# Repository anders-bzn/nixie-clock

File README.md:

# About the Nixie Clock

This is a clock powered by a Raspberry Pi Zero W. It fetches current time by 
NTP and must be connected to a WiFi network to display the time.

The time is displayed on six IN-14 nixie tubes driven by six 74141. No 
multiplexing! The intensity can be adjusted by PWM.

## PCB's 
There are in total five PCB's in this project. All boards are drawn with KiCad 8.0.

### Board nixie-bottom
Bottom lid, no electrical function.

### Board nixie-clock
The main board, it hold gpio-expanders and driver IC's for the tubes. It
also connects to the PSU board, Raspberry Pi and the nixie tube board.

### Board nixie-clock-psu
Power supply board, creates 5V DC and 170V DC from 12V DC. The 170V is created by a step up converter built using a MAX1771 IC. The 5V is created by a integrated switched regulator.

### Board nixie-clock-tubes
Upper board on which all tubes are mounted.

### Board nixie-top
Top lid, no electrical function.

### Software
The clocks software is written in Python. It's just a simple poll loop that set the new time on gpio's on the gpio-expanders every time the second changes. It's started as a systemd service at boot time.

To install the software on the Raspberry Pi, copy the [./sw](sw/) folder to the Raspberry Pi and install the software by:

```
$ sudo ./clock-setup.sh
$ sudo reboot
```

NOTE: [./sw/timesyncd.conf](sw/timesyncd.conf) is an example.

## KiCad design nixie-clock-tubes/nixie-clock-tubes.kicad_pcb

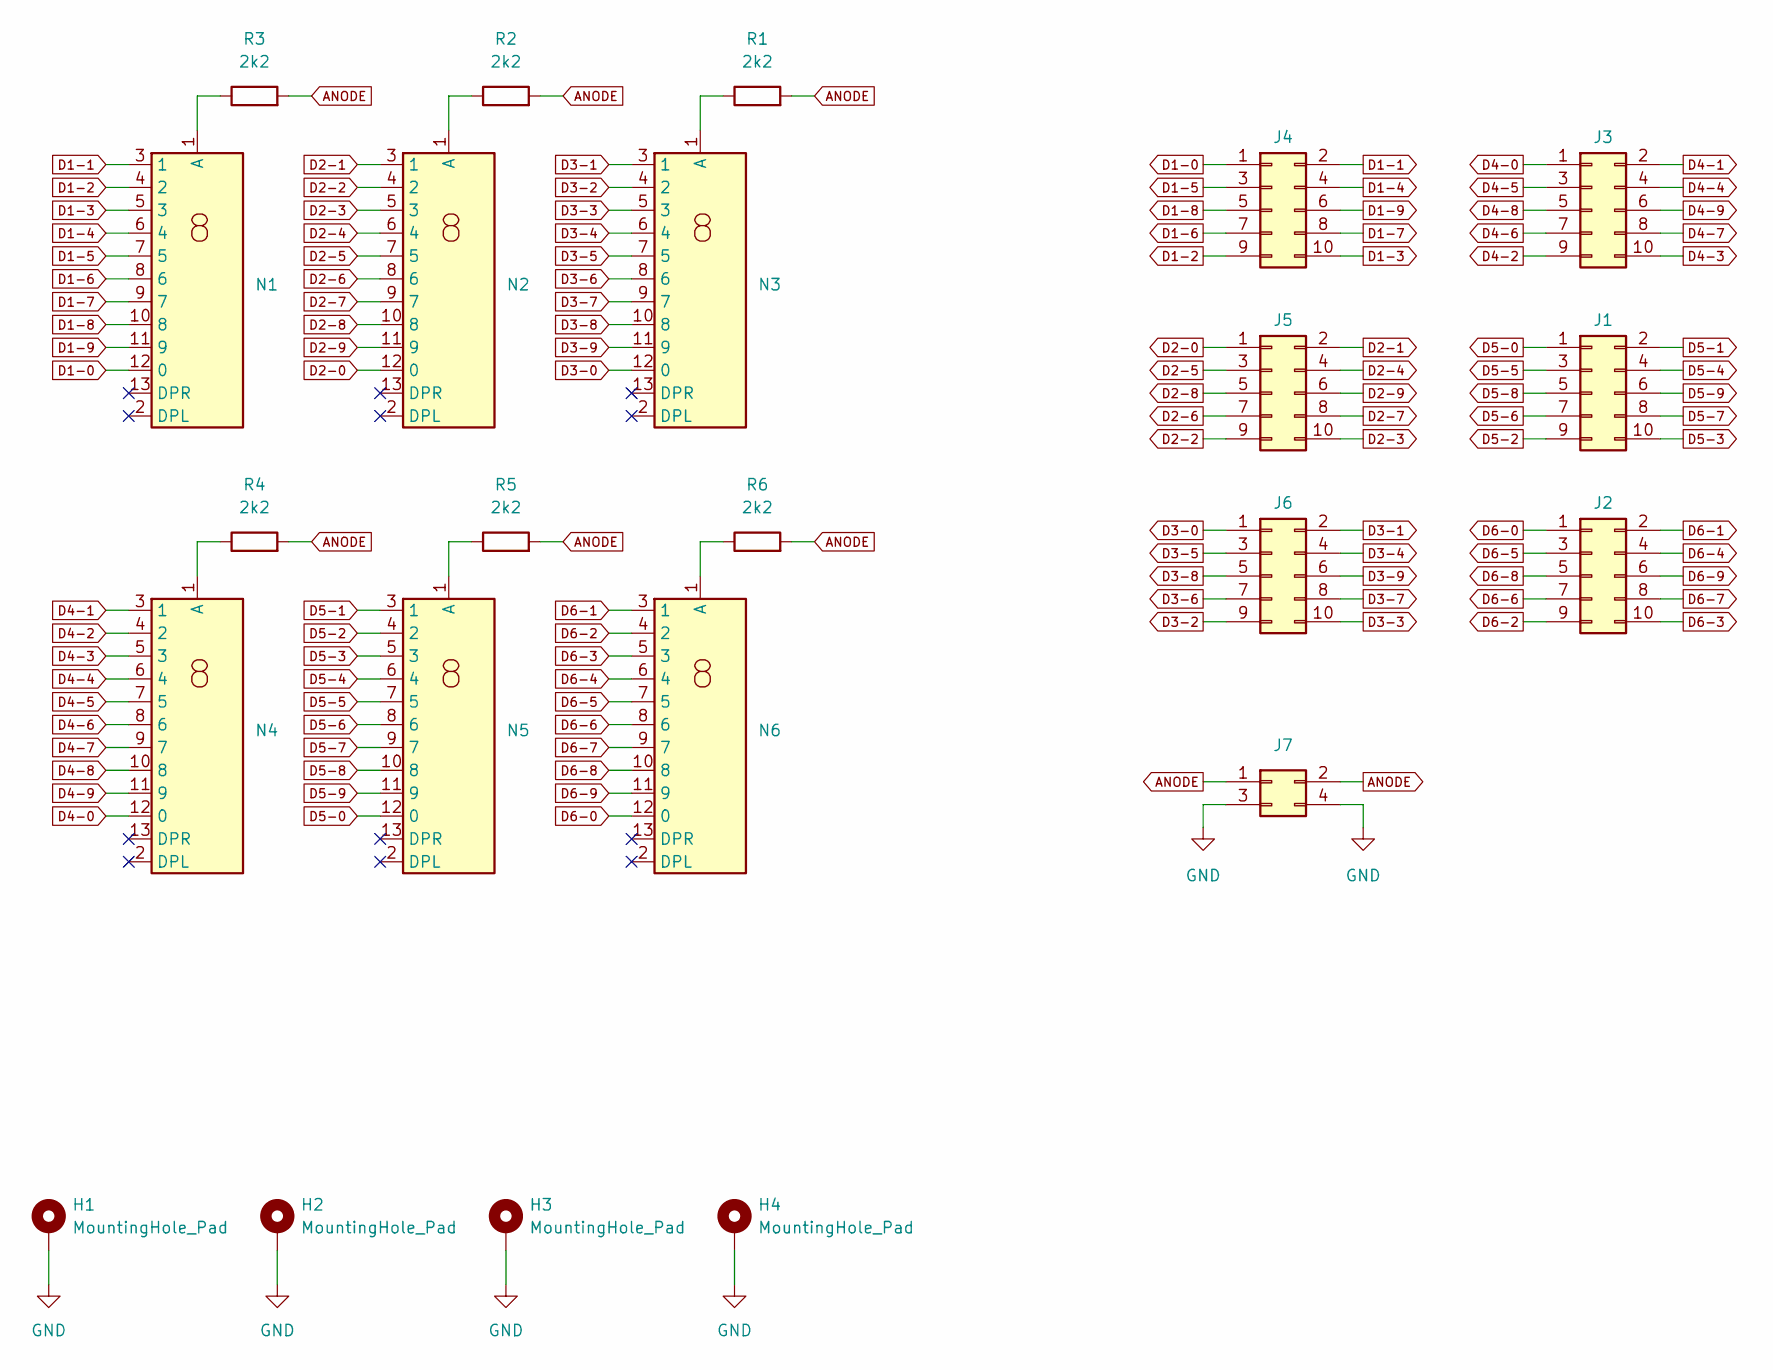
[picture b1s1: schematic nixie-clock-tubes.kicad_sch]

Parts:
H1, H2, H3, H4: MountingHole_Pad; MountingHole_2.7mm_M2.5_DIN965_Pad
J1, J2, J3, J4, J5, J6: Conn_02x05_Odd_Even; PinSocket_2x05_P2.00mm_Vertical
J7: Conn_02x02_Odd_Even; PinSocket_2x02_P2.00mm_Vertical
N1, N2, N3, N4, N5, N6: IN-14
R1, R2, R3, R4, R5, R6: 2k2; R_1206_3216Metric

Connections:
ANODE: J7.1, J7.2, R1.2, R2.2, R3.2, R4.2, R5.2, R6.2
D1-0: J4.1, N1.12 (0)
D1-1: J4.2, N1.3 (1)
D1-2: J4.9, N1.4 (2)
D1-3: J4.10, N1.5 (3)
D1-4: J4.4, N1.6 (4)
D1-5: J4.3, N1.7 (5)
D1-6: J4.7, N1.8 (6)
D1-7: J4.8, N1.9 (7)
D1-8: J4.5, N1.10 (8)
D1-9: J4.6, N1.11 (9)
D2-0: J5.1, N2.12 (0)
D2-1: J5.2, N2.3 (1)
D2-2: J5.9, N2.4 (2)
D2-3: J5.10, N2.5 (3)
D2-4: J5.4, N2.6 (4)
D2-5: J5.3, N2.7 (5)
D2-6: J5.7, N2.8 (6)
D2-7: J5.8, N2.9 (7)
D2-8: J5.5, N2.10 (8)
D2-9: J5.6, N2.11 (9)
D3-0: J6.1, N3.12 (0)
D3-1: J6.2, N3.3 (1)
D3-2: J6.9, N3.4 (2)
D3-3: J6.10, N3.5 (3)
D3-4: J6.4, N3.6 (4)
D3-5: J6.3, N3.7 (5)
D3-6: J6.7, N3.8 (6)
D3-7: J6.8, N3.9 (7)
D3-8: J6.5, N3.10 (8)
D3-9: J6.6, N3.11 (9)
D4-0: J3.1, N4.12 (0)
D4-1: J3.2, N4.3 (1)
D4-2: J3.9, N4.4 (2)
D4-3: J3.10, N4.5 (3)
D4-4: J3.4, N4.6 (4)
D4-5: J3.3, N4.7 (5)
D4-6: J3.7, N4.8 (6)
D4-7: J3.8, N4.9 (7)
D4-8: J3.5, N4.10 (8)
D4-9: J3.6, N4.11 (9)
D5-0: J1.1, N5.12 (0)
D5-1: J1.2, N5.3 (1)
D5-2: J1.9, N5.4 (2)
D5-3: J1.10, N5.5 (3)
D5-4: J1.4, N5.6 (4)
D5-5: J1.3, N5.7 (5)
D5-6: J1.7, N5.8 (6)
D5-7: J1.8, N5.9 (7)
D5-8: J1.5, N5.10 (8)
D5-9: J1.6, N5.11 (9)
D6-0: J2.1, N6.12 (0)
D6-1: J2.2, N6.3 (1)
D6-2: J2.9, N6.4 (2)
D6-3: J2.10, N6.5 (3)
D6-4: J2.4, N6.6 (4)
D6-5: J2.3, N6.7 (5)
D6-6: J2.7, N6.8 (6)
D6-7: J2.8, N6.9 (7)
D6-8: J2.5, N6.10 (8)
D6-9: J2.6, N6.11 (9)
GND: H1.1, H2.1, H3.1, H4.1, J7.3, J7.4
unnamed: N1.1 (A), R3.1
unnamed: N2.1 (A), R2.1
unnamed: N3.1 (A), R1.1
unnamed: N4.1 (A), R4.1
unnamed: N5.1 (A), R5.1
unnamed: N6.1 (A), R6.1

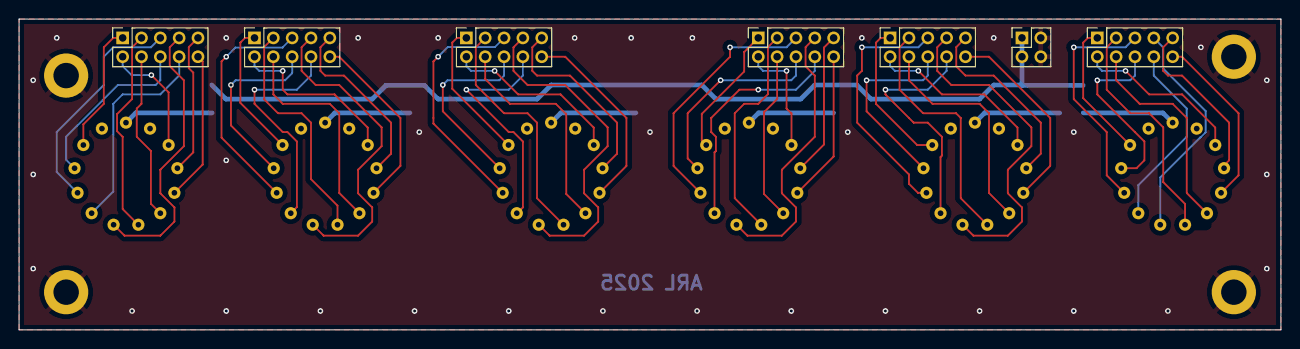
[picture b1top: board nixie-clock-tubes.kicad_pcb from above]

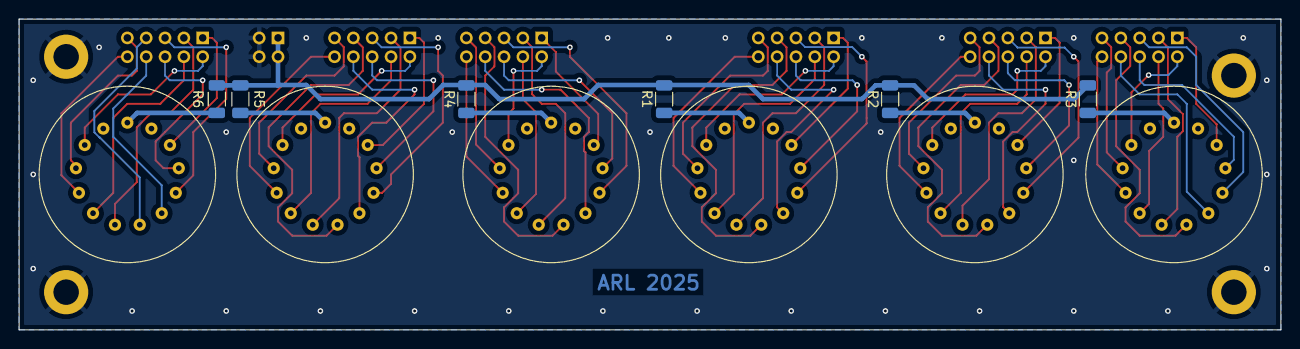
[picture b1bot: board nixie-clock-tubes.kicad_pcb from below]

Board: 2 copper layers, 134.0 x 33.0 mm, 23 parts (12 on the bottom side), 68 nets.

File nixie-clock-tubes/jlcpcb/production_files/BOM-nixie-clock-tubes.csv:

Comment,Designator,Footprint,LCSC,Quantity
~,N6,IN-14,,1
~,N5,IN-14,,1
~,N4,IN-14,,1
~,N3,IN-14,,1
~,N2,IN-14,,1
~,N1,IN-14,,1
Conn_02x02_Odd_Even,J7,PinSocket_2x02_P2.00mm_Vertical,,1
Conn_02x05_Odd_Even,J6,PinSocket_2x05_P2.00mm_Vertical,,1
Conn_02x05_Odd_Even,J5,PinSocket_2x05_P2.00mm_Vertical,,1
Conn_02x05_Odd_Even,J4,PinSocket_2x05_P2.00mm_Vertical,,1
Conn_02x05_Odd_Even,J3,PinSocket_2x05_P2.00mm_Vertical,,1
Conn_02x05_Odd_Even,J2,PinSocket_2x05_P2.00mm_Vertical,,1
Conn_02x05_Odd_Even,J1,PinSocket_2x05_P2.00mm_Vertical,,1
2k2,R6,R_1206_3216Metric,,1
2k2,R5,R_1206_3216Metric,,1
2k2,R4,R_1206_3216Metric,,1
2k2,R3,R_1206_3216Metric,,1
2k2,R2,R_1206_3216Metric,,1
2k2,R1,R_1206_3216Metric,,1

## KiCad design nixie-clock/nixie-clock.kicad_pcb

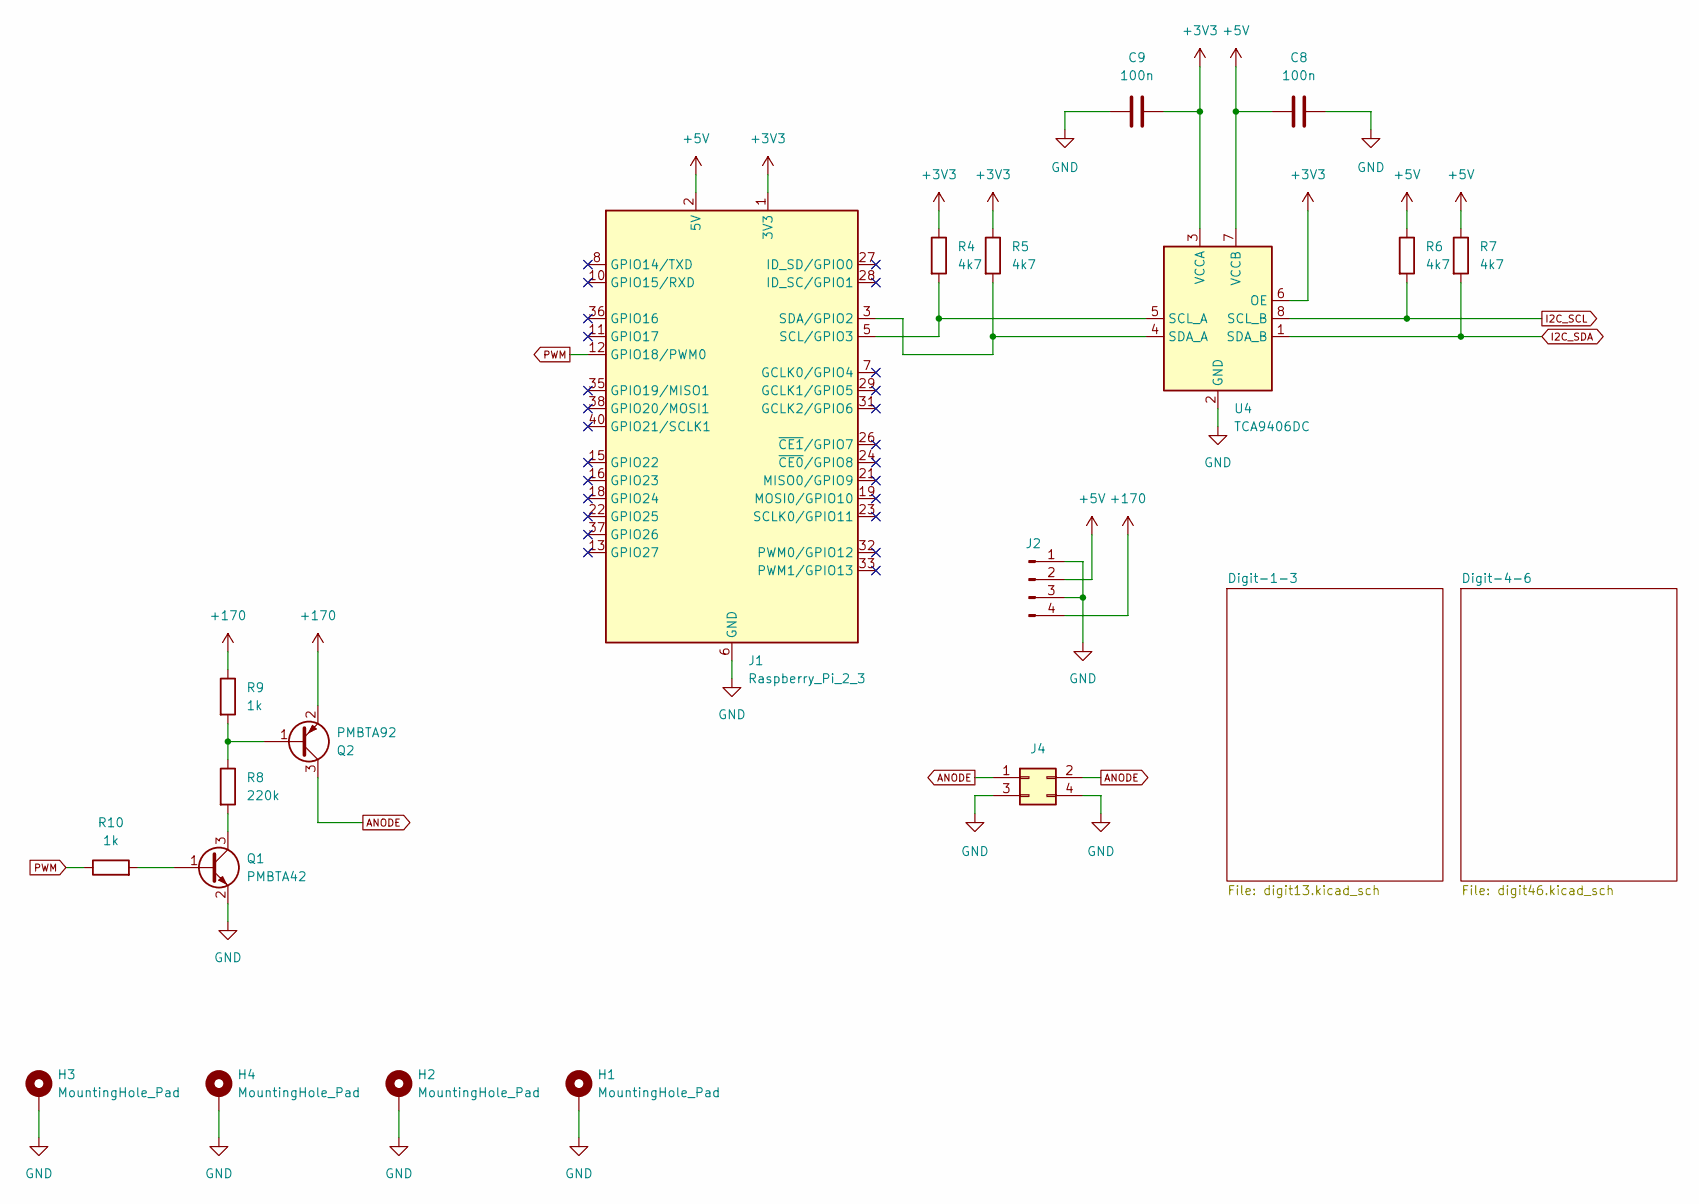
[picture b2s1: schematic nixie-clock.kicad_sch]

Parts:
C8, C9: 100n; C_0805_2012Metric_Pad1.18x1.45mm_HandSolder
H1, H2, H3, H4: MountingHole_Pad; MountingHole_2.7mm_M2.5_DIN965_Pad
J1: Raspberry_Pi_2_3; Raspberry_Pi_Zero_Socketed_THT_FaceDown_MountingHoles
J2: Conn_01x04_Pin; PinHeader_1x04_P2.54mm_Vertical
J4: Conn_02x02_Odd_Even; PinHeader_2x02_P2.00mm_Vertical
Q1: PMBTA42; SOT-23
Q2: PMBTA92; SOT-23
R4, R5, R6, R7: 4k7; R_0805_2012Metric_Pad1.20x1.40mm_HandSolder
R8: 220k; R_1206_3216Metric_Pad1.30x1.75mm_HandSolder
R9: 1k; R_1206_3216Metric_Pad1.30x1.75mm_HandSolder
R10: 1k; R_0805_2012Metric_Pad1.20x1.40mm_HandSolder
U4: TCA9406DC; SSOP-8_2.95x2.8mm_P0.65mm

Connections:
+3V3: C9.1, J1.1 (3V3), J1.17 (3V3), R4.1, R5.1, U4.3 (VCCA), U4.6 (OE)
+5V: C8.1, J1.2 (5V), J1.4 (5V), J2.2, R6.1, R7.1, U4.7 (VCCB); also elsewhere on the board
+170: J2.4, Q2.2 (E), R9.1
ANODE: J4.1, J4.2, Q2.3 (C)
GND: C8.2, C9.2, H1.1, H2.1, H3.1, H4.1, J1.6 (GND), J1.9 (GND), J1.14 (GND), J1.20 (GND), J1.25 (GND), J1.30 (GND), J1.34 (GND), J1.39 (GND), J2.1, J2.3, J4.3, J4.4, Q1.2 (E), U4.2 (GND); also elsewhere on the board
I2C_SCL: R6.2, U4.8 (SCL_B); also elsewhere on the board
I2C_SDA: R7.2, U4.1 (SDA_B); also elsewhere on the board
unnamed: J1.5 (SCL/GPIO3), R4.2, U4.5 (SCL_A)
unnamed: J1.3 (SDA/GPIO2), R5.2, U4.4 (SDA_A)
unnamed: Q1.1 (B), R10.2
unnamed: Q1.3 (C), R8.2
unnamed: Q2.1 (B), R8.1, R9.2
PWM: J1.12 (GPIO18/PWM0), R10.1

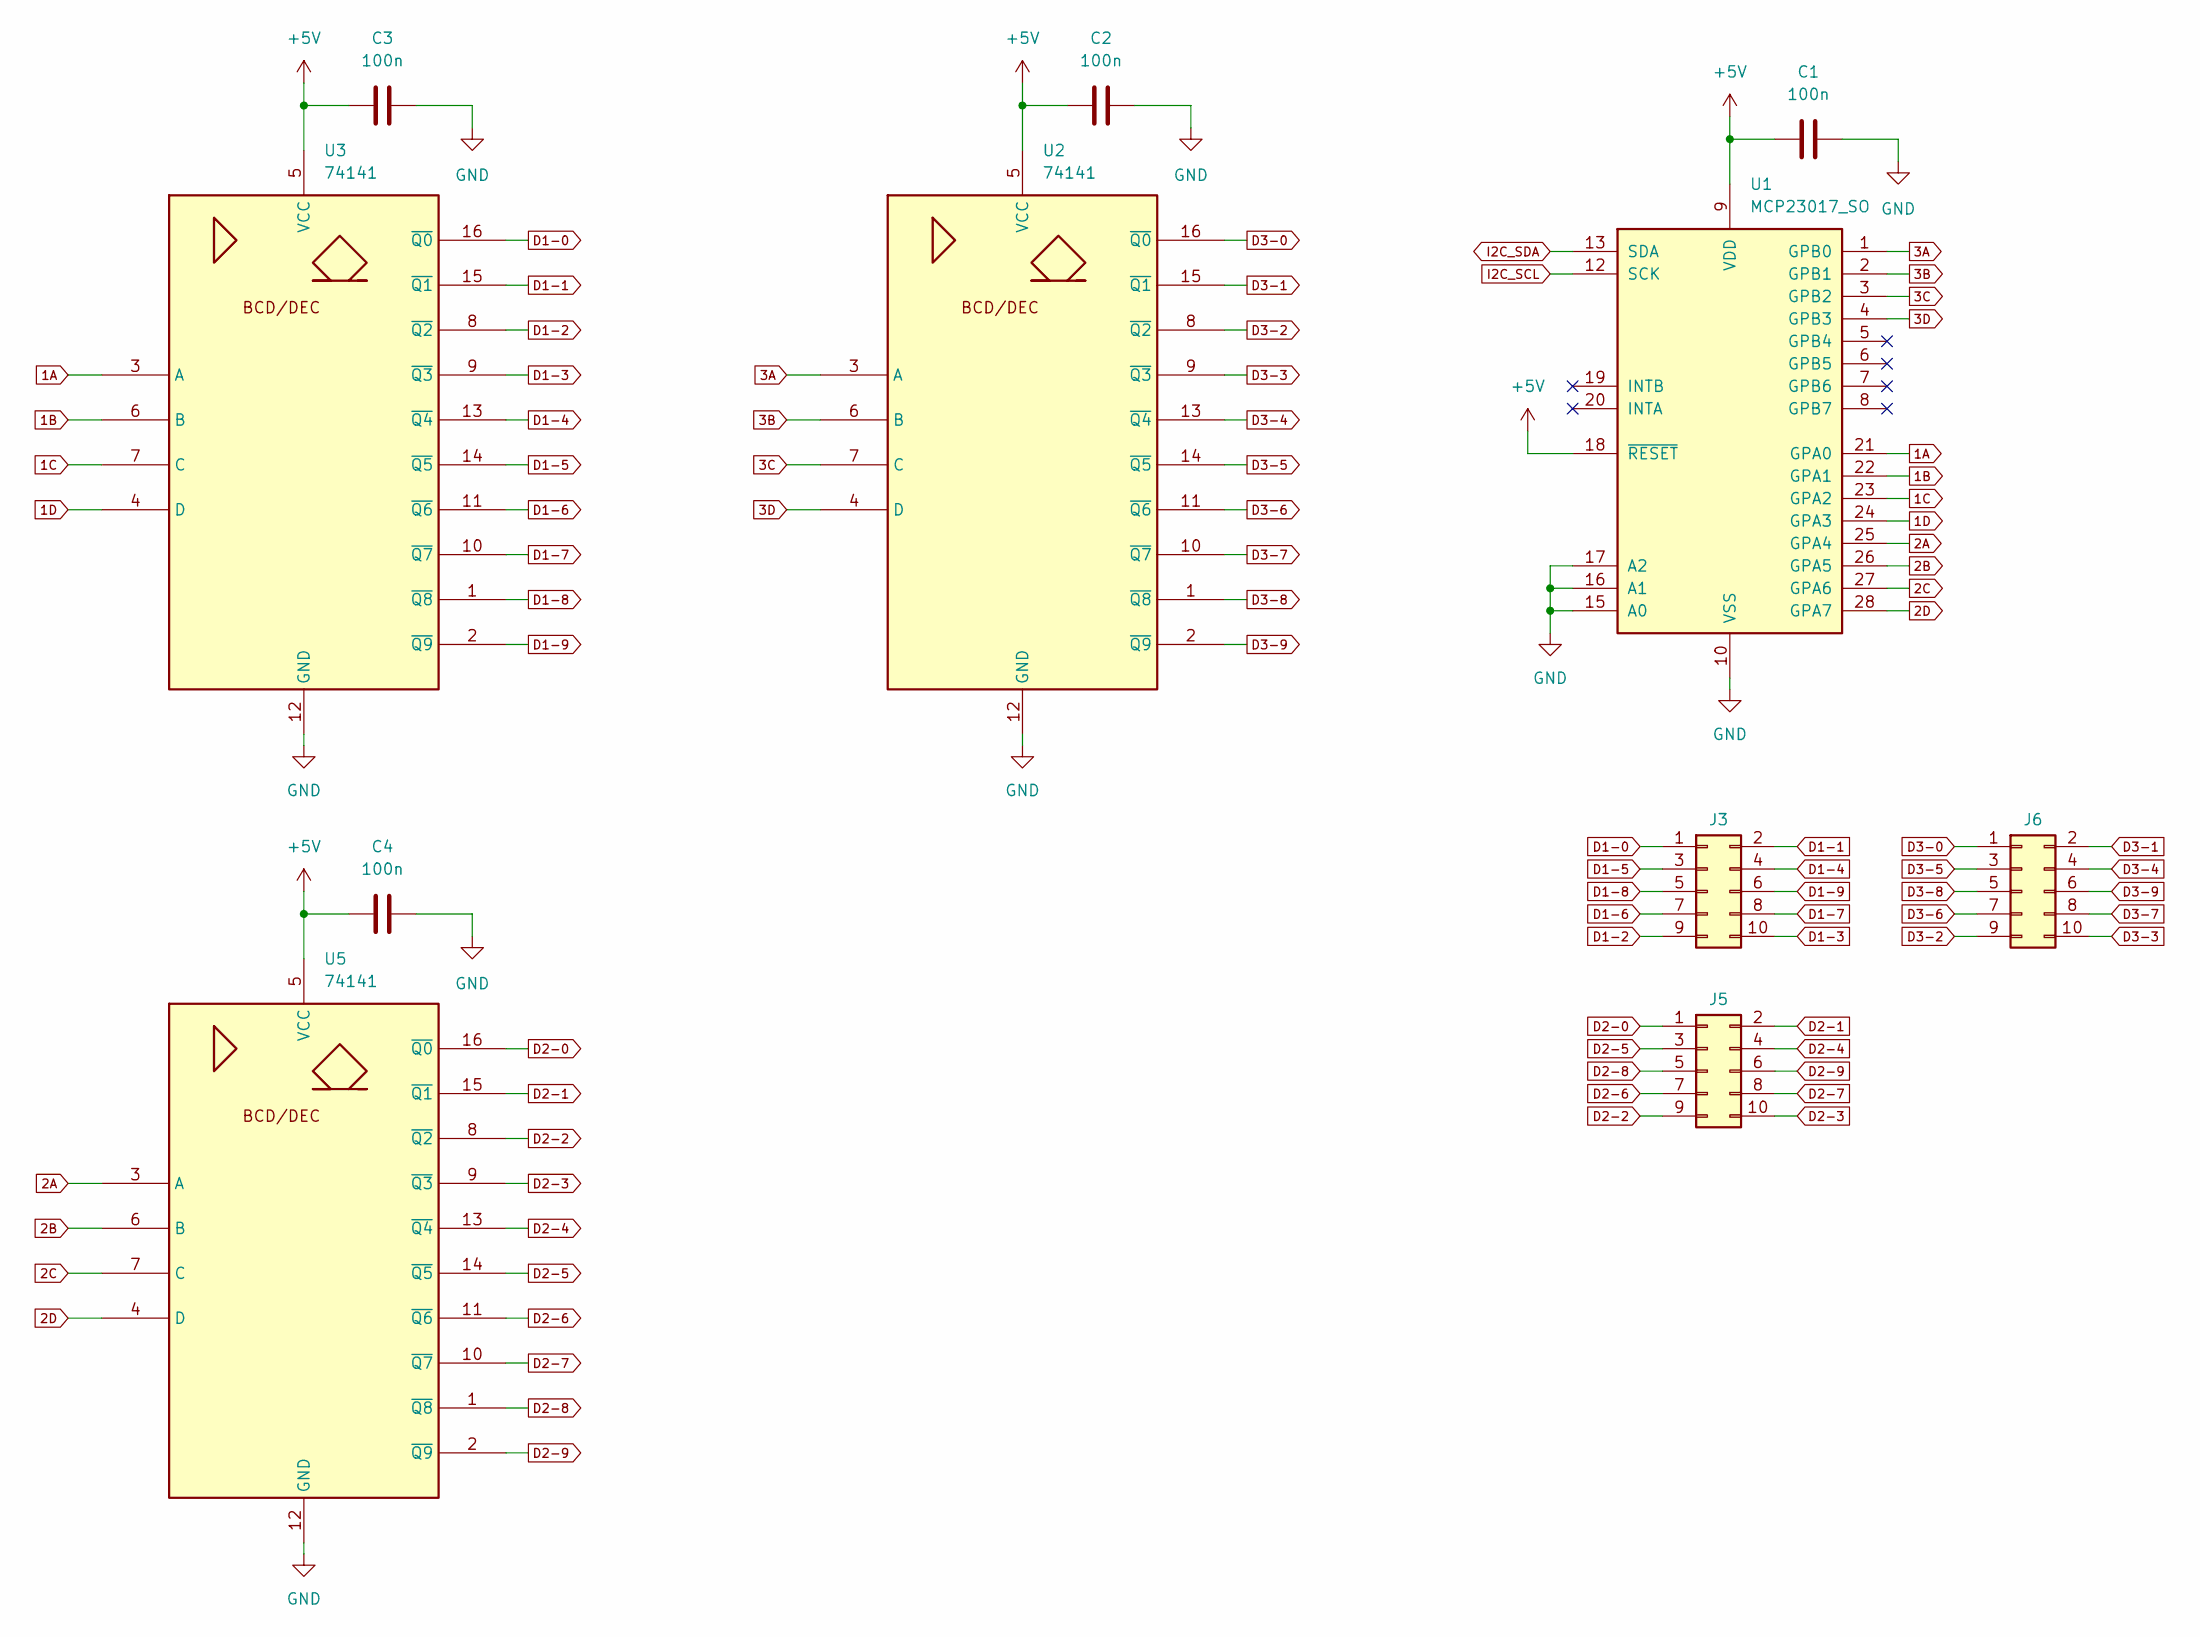
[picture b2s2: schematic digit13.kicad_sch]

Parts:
C1, C2, C3, C4: 100n; C_0805_2012Metric_Pad1.18x1.45mm_HandSolder
J3, J5, J6: Conn_02x05_Odd_Even; PinHeader_2x05_P2.00mm_Vertical
U1: MCP23017_SO; SSOP-28_5.3x10.2mm_P0.65mm
U2, U3, U5: 74141; DIP-16_W7.62mm

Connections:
1A: U1.21 (GPA0), U3.3 (A)
1B: U1.22 (GPA1), U3.6 (B)
1C: U1.23 (GPA2), U3.7 (C)
1D: U1.24 (GPA3), U3.4 (D)
2A: U1.25 (GPA4), U5.3 (A)
2B: U1.26 (GPA5), U5.6 (B)
2C: U1.27 (GPA6), U5.7 (C)
2D: U1.28 (GPA7), U5.4 (D)
3A: U1.1 (GPB0), U2.3 (A)
3B: U1.2 (GPB1), U2.6 (B)
3C: U1.3 (GPB2), U2.7 (C)
3D: U1.4 (GPB3), U2.4 (D)
+5V: C1.1, C2.1, C3.1, C4.1, U1.9 (VDD), U1.18 (~RESET), U2.5 (VCC), U3.5 (VCC), U5.5 (VCC); also elsewhere on the board
D1-0: J3.1, U3.16 (~Q0)
D1-1: J3.2, U3.15 (~Q1)
D1-2: J3.9, U3.8 (~Q2)
D1-3: J3.10, U3.9 (~Q3)
D1-4: J3.4, U3.13 (~Q4)
D1-5: J3.3, U3.14 (~Q5)
D1-6: J3.7, U3.11 (~Q6)
D1-7: J3.8, U3.10 (~Q7)
D1-8: J3.5, U3.1 (~Q8)
D1-9: J3.6, U3.2 (~Q9)
D2-0: J5.1, U5.16 (~Q0)
D2-1: J5.2, U5.15 (~Q1)
D2-2: J5.9, U5.8 (~Q2)
D2-3: J5.10, U5.9 (~Q3)
D2-4: J5.4, U5.13 (~Q4)
D2-5: J5.3, U5.14 (~Q5)
D2-6: J5.7, U5.11 (~Q6)
D2-7: J5.8, U5.10 (~Q7)
D2-8: J5.5, U5.1 (~Q8)
D2-9: J5.6, U5.2 (~Q9)
D3-0: J6.1, U2.16 (~Q0)
D3-1: J6.2, U2.15 (~Q1)
D3-2: J6.9, U2.8 (~Q2)
D3-3: J6.10, U2.9 (~Q3)
D3-4: J6.4, U2.13 (~Q4)
D3-5: J6.3, U2.14 (~Q5)
D3-6: J6.7, U2.11 (~Q6)
D3-7: J6.8, U2.10 (~Q7)
D3-8: J6.5, U2.1 (~Q8)
D3-9: J6.6, U2.2 (~Q9)
GND: C1.2, C2.2, C3.2, C4.2, U1.10 (VSS), U1.15 (A0), U1.16 (A1), U1.17 (A2), U2.12 (GND), U3.12 (GND), U5.12 (GND); also elsewhere on the board
I2C_SCL: U1.12 (SCK); also elsewhere on the board
I2C_SDA: U1.13 (SDA); also elsewhere on the board

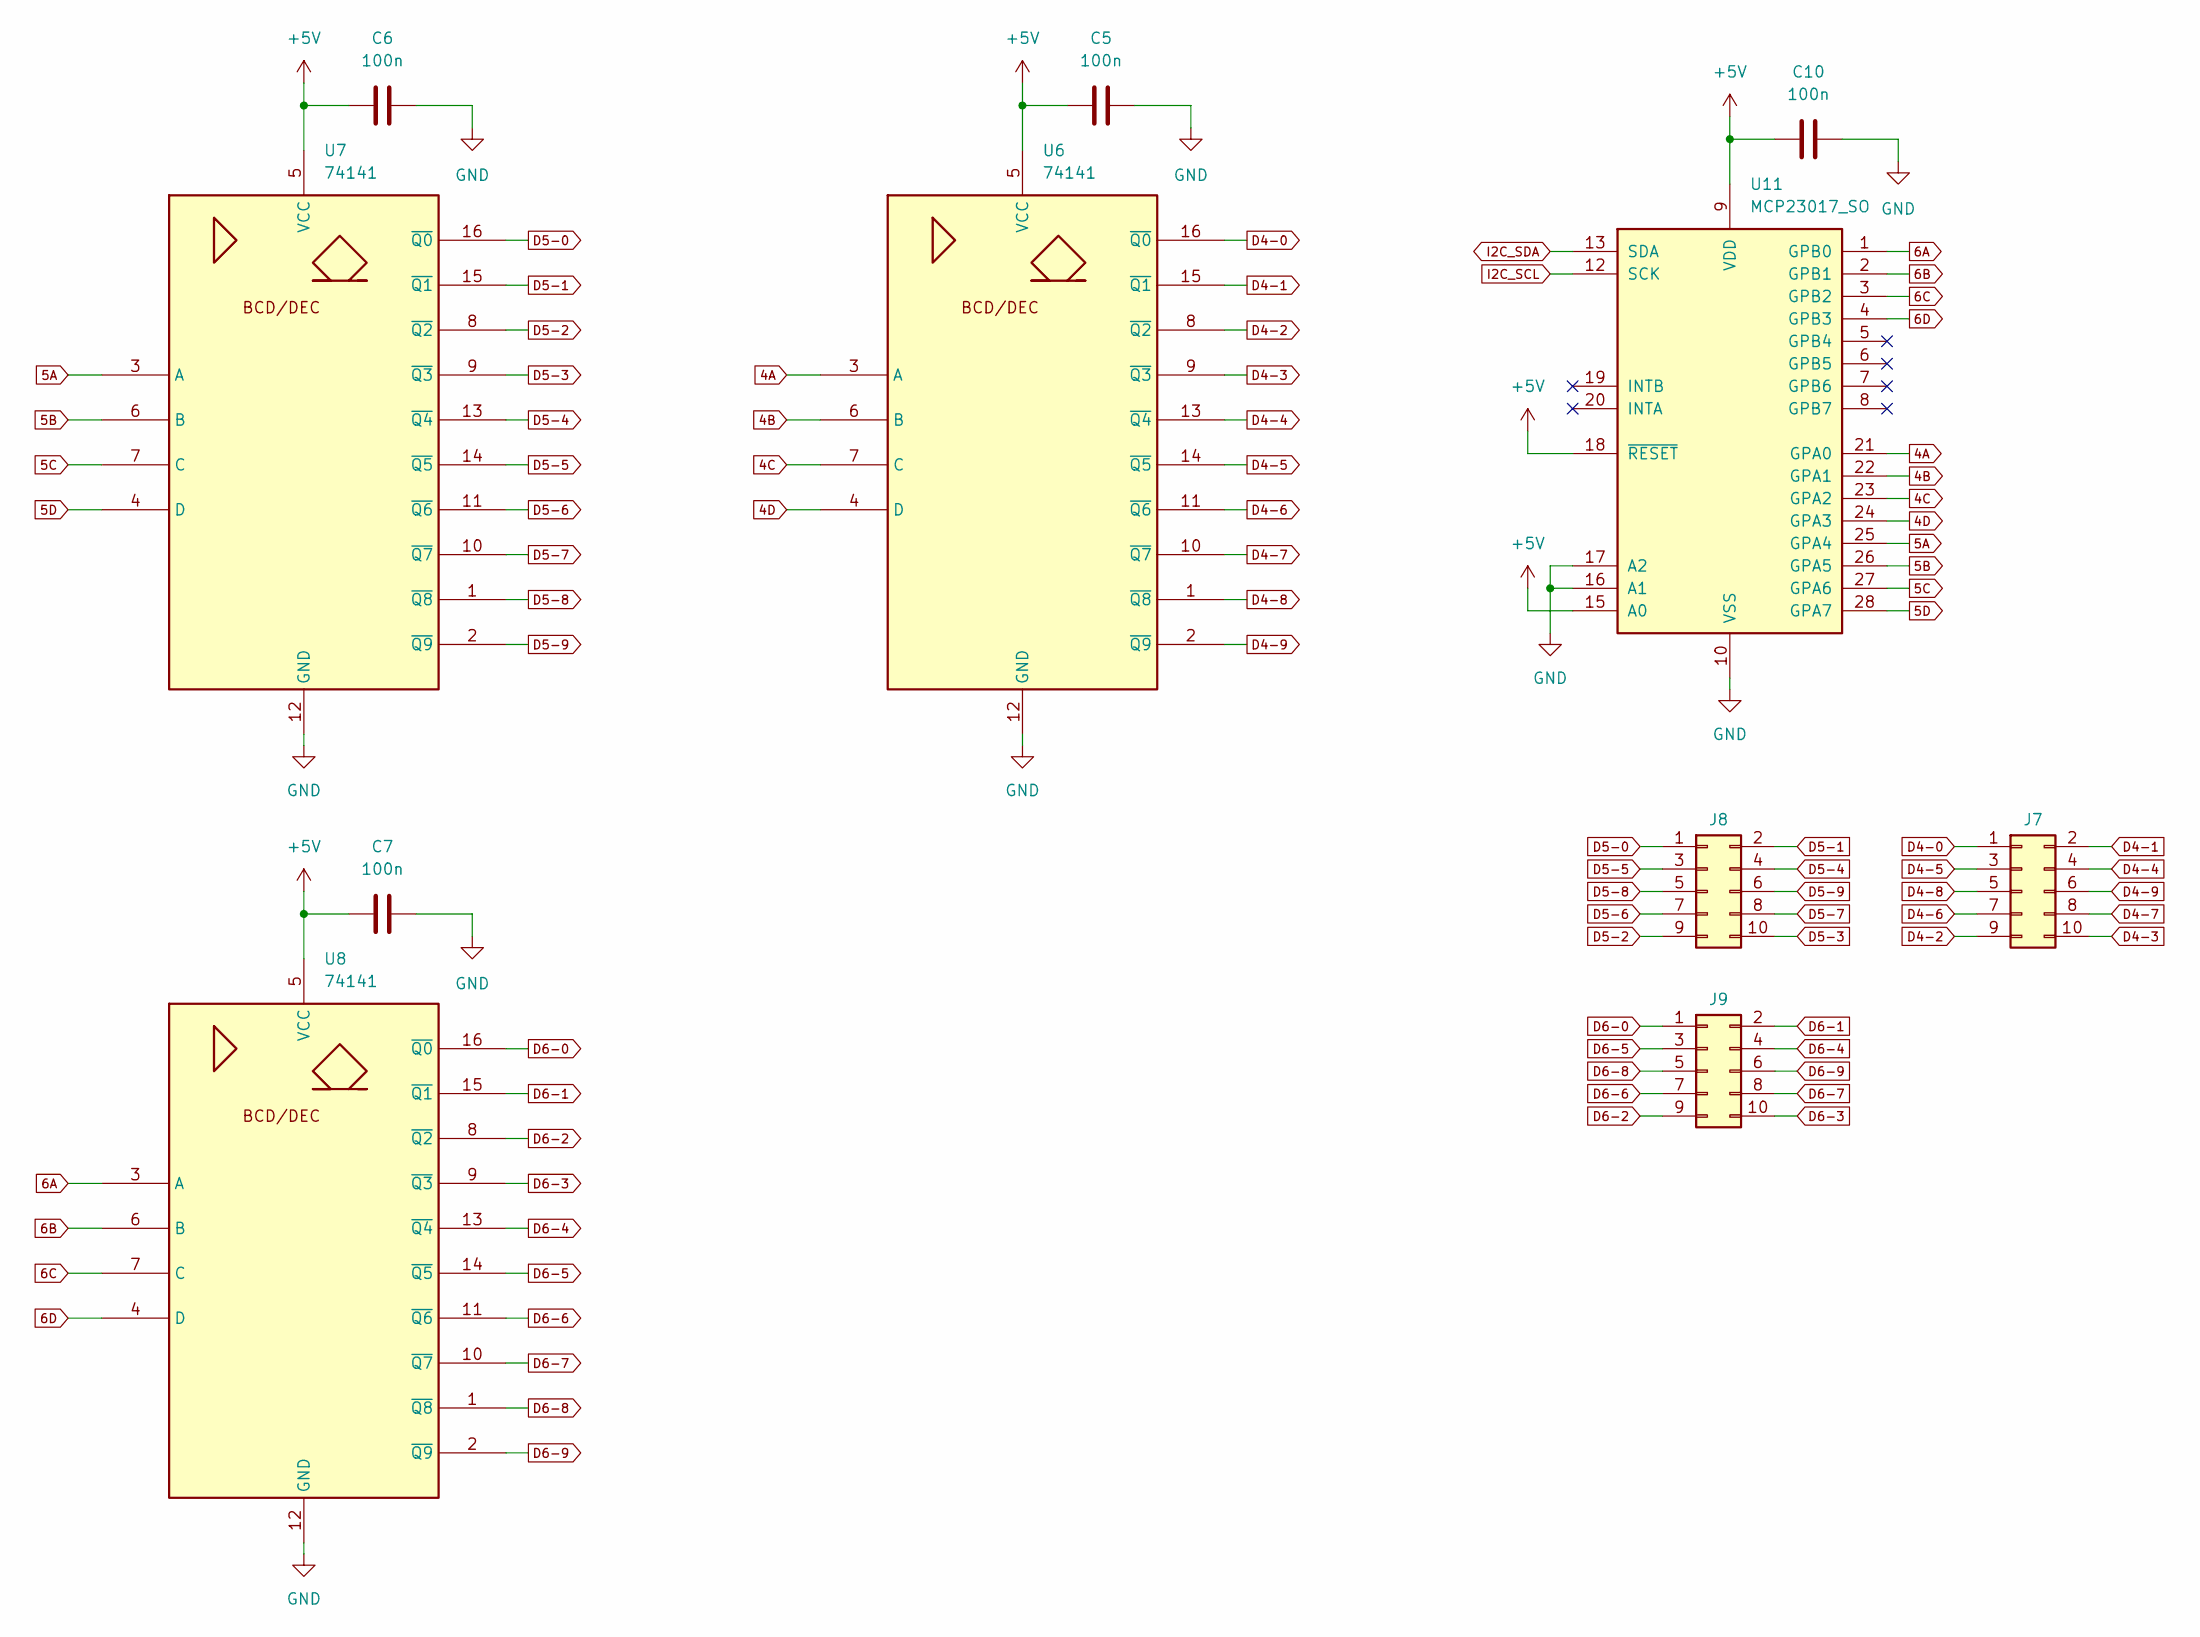
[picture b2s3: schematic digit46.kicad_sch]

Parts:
C5, C6, C7, C10: 100n; C_0805_2012Metric_Pad1.18x1.45mm_HandSolder
J7, J8, J9: Conn_02x05_Odd_Even; PinHeader_2x05_P2.00mm_Vertical
U6, U7, U8: 74141; DIP-16_W7.62mm
U11: MCP23017_SO; SSOP-28_5.3x10.2mm_P0.65mm

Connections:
4A: U6.3 (A), U11.21 (GPA0)
4B: U6.6 (B), U11.22 (GPA1)
4C: U6.7 (C), U11.23 (GPA2)
4D: U6.4 (D), U11.24 (GPA3)
5A: U7.3 (A), U11.25 (GPA4)
5B: U7.6 (B), U11.26 (GPA5)
5C: U7.7 (C), U11.27 (GPA6)
5D: U7.4 (D), U11.28 (GPA7)
6A: U8.3 (A), U11.1 (GPB0)
6B: U8.6 (B), U11.2 (GPB1)
6C: U8.7 (C), U11.3 (GPB2)
6D: U8.4 (D), U11.4 (GPB3)
+5V: C5.1, C6.1, C7.1, C10.1, U6.5 (VCC), U7.5 (VCC), U8.5 (VCC), U11.9 (VDD), U11.15 (A0), U11.18 (~RESET); also elsewhere on the board
D4-0: J7.1, U6.16 (~Q0)
D4-1: J7.2, U6.15 (~Q1)
D4-2: J7.9, U6.8 (~Q2)
D4-3: J7.10, U6.9 (~Q3)
D4-4: J7.4, U6.13 (~Q4)
D4-5: J7.3, U6.14 (~Q5)
D4-6: J7.7, U6.11 (~Q6)
D4-7: J7.8, U6.10 (~Q7)
D4-8: J7.5, U6.1 (~Q8)
D4-9: J7.6, U6.2 (~Q9)
D5-0: J8.1, U7.16 (~Q0)
D5-1: J8.2, U7.15 (~Q1)
D5-2: J8.9, U7.8 (~Q2)
D5-3: J8.10, U7.9 (~Q3)
D5-4: J8.4, U7.13 (~Q4)
D5-5: J8.3, U7.14 (~Q5)
D5-6: J8.7, U7.11 (~Q6)
D5-7: J8.8, U7.10 (~Q7)
D5-8: J8.5, U7.1 (~Q8)
D5-9: J8.6, U7.2 (~Q9)
D6-0: J9.1, U8.16 (~Q0)
D6-1: J9.2, U8.15 (~Q1)
D6-2: J9.9, U8.8 (~Q2)
D6-3: J9.10, U8.9 (~Q3)
D6-4: J9.4, U8.13 (~Q4)
D6-5: J9.3, U8.14 (~Q5)
D6-6: J9.7, U8.11 (~Q6)
D6-7: J9.8, U8.10 (~Q7)
D6-8: J9.5, U8.1 (~Q8)
D6-9: J9.6, U8.2 (~Q9)
GND: C5.2, C6.2, C7.2, C10.2, U6.12 (GND), U7.12 (GND), U8.12 (GND), U11.10 (VSS), U11.16 (A1), U11.17 (A2); also elsewhere on the board
I2C_SCL: U11.12 (SCK); also elsewhere on the board
I2C_SDA: U11.13 (SDA); also elsewhere on the board

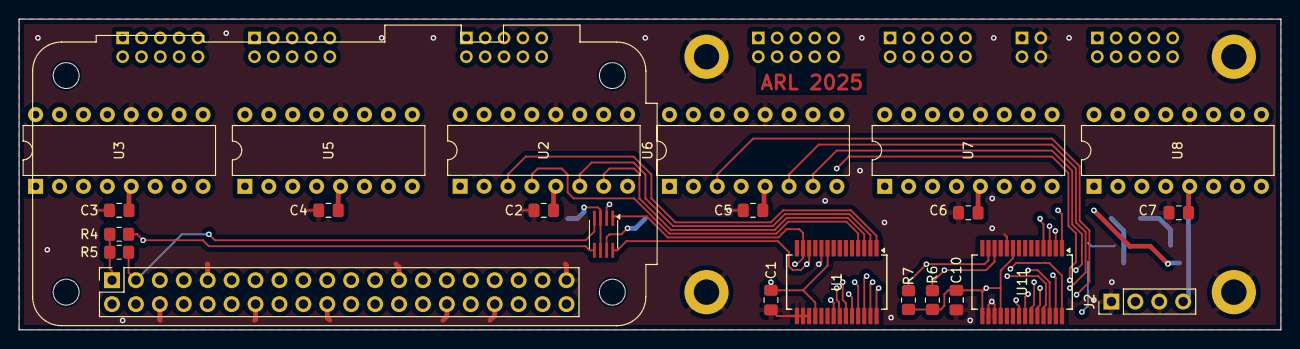
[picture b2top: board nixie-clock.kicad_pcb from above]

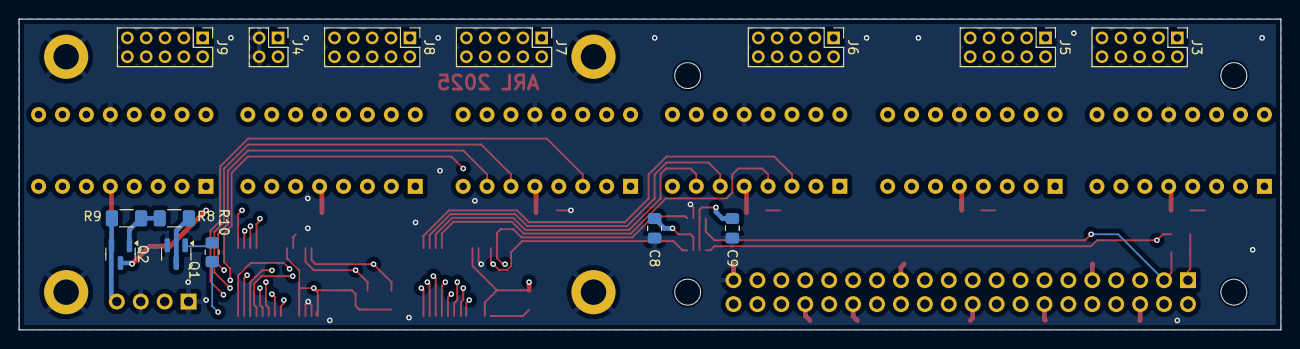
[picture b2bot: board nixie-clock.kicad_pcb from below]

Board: 4 copper layers, 134.0 x 33.0 mm, 41 parts (14 on the bottom side), 97 nets.

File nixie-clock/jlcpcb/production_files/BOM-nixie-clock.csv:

Comment,Designator,Footprint,LCSC,Quantity
1k,R10,R_0805_2012Metric_Pad1.20x1.40mm_HandSolder,,1
1k,R9,R_1206_3216Metric_Pad1.30x1.75mm_HandSolder,,1
220k,R8,R_1206_3216Metric_Pad1.30x1.75mm_HandSolder,,1
PMBTA92,Q2,SOT-23,,1
PMBTA42,Q1,SOT-23,,1
100n,C9,C_0805_2012Metric_Pad1.18x1.45mm_HandSolder,,1
100n,C8,C_0805_2012Metric_Pad1.18x1.45mm_HandSolder,,1
74141,U6,DIP-16_W7.62mm,,1
Conn_02x05_Odd_Even,J7,PinHeader_2x05_P2.00mm_Vertical,,1
100n,C5,C_0805_2012Metric_Pad1.18x1.45mm_HandSolder,,1
Conn_02x05_Odd_Even,J9,PinHeader_2x05_P2.00mm_Vertical,,1
Conn_02x05_Odd_Even,J8,PinHeader_2x05_P2.00mm_Vertical,,1
Conn_02x05_Odd_Even,J6,PinHeader_2x05_P2.00mm_Vertical,,1
Conn_02x05_Odd_Even,J5,PinHeader_2x05_P2.00mm_Vertical,,1
Conn_02x02_Odd_Even,J4,PinHeader_2x02_P2.00mm_Vertical,,1
Conn_02x05_Odd_Even,J3,PinHeader_2x05_P2.00mm_Vertical,,1
Conn_01x04_Pin,J2,PinHeader_1x04_P2.54mm_Vertical,,1
TCA9406DC,U4,SSOP-8_2.95x2.8mm_P0.65mm,,1
4k7,R7,R_0805_2012Metric_Pad1.20x1.40mm_HandSolder,,1
4k7,R6,R_0805_2012Metric_Pad1.20x1.40mm_HandSolder,,1
MCP23017_SO,U11,SSOP-28_5.3x10.2mm_P0.65mm,,1
74141,U8,DIP-16_W7.62mm,,1
74141,U7,DIP-16_W7.62mm,,1
100n,C10,C_0805_2012Metric_Pad1.18x1.45mm_HandSolder,,1
100n,C7,C_0805_2012Metric_Pad1.18x1.45mm_HandSolder,,1
100n,C6,C_0805_2012Metric_Pad1.18x1.45mm_HandSolder,,1
MCP23017_SO,U1,SSOP-28_5.3x10.2mm_P0.65mm,,1
74141,U5,DIP-16_W7.62mm,,1
74141,U3,DIP-16_W7.62mm,,1
74141,U2,DIP-16_W7.62mm,,1
4k7,R5,R_0805_2012Metric_Pad1.20x1.40mm_HandSolder,,1
4k7,R4,R_0805_2012Metric_Pad1.20x1.40mm_HandSolder,,1
100n,C4,C_0805_2012Metric_Pad1.18x1.45mm_HandSolder,,1
100n,C3,C_0805_2012Metric_Pad1.18x1.45mm_HandSolder,,1
100n,C2,C_0805_2012Metric_Pad1.18x1.45mm_HandSolder,,1
100n,C1,C_0805_2012Metric_Pad1.18x1.45mm_HandSolder,,1
Raspberry_Pi_2_3,J1,Raspberry_Pi_Zero_Socketed_THT_FaceDown_MountingHoles,,1

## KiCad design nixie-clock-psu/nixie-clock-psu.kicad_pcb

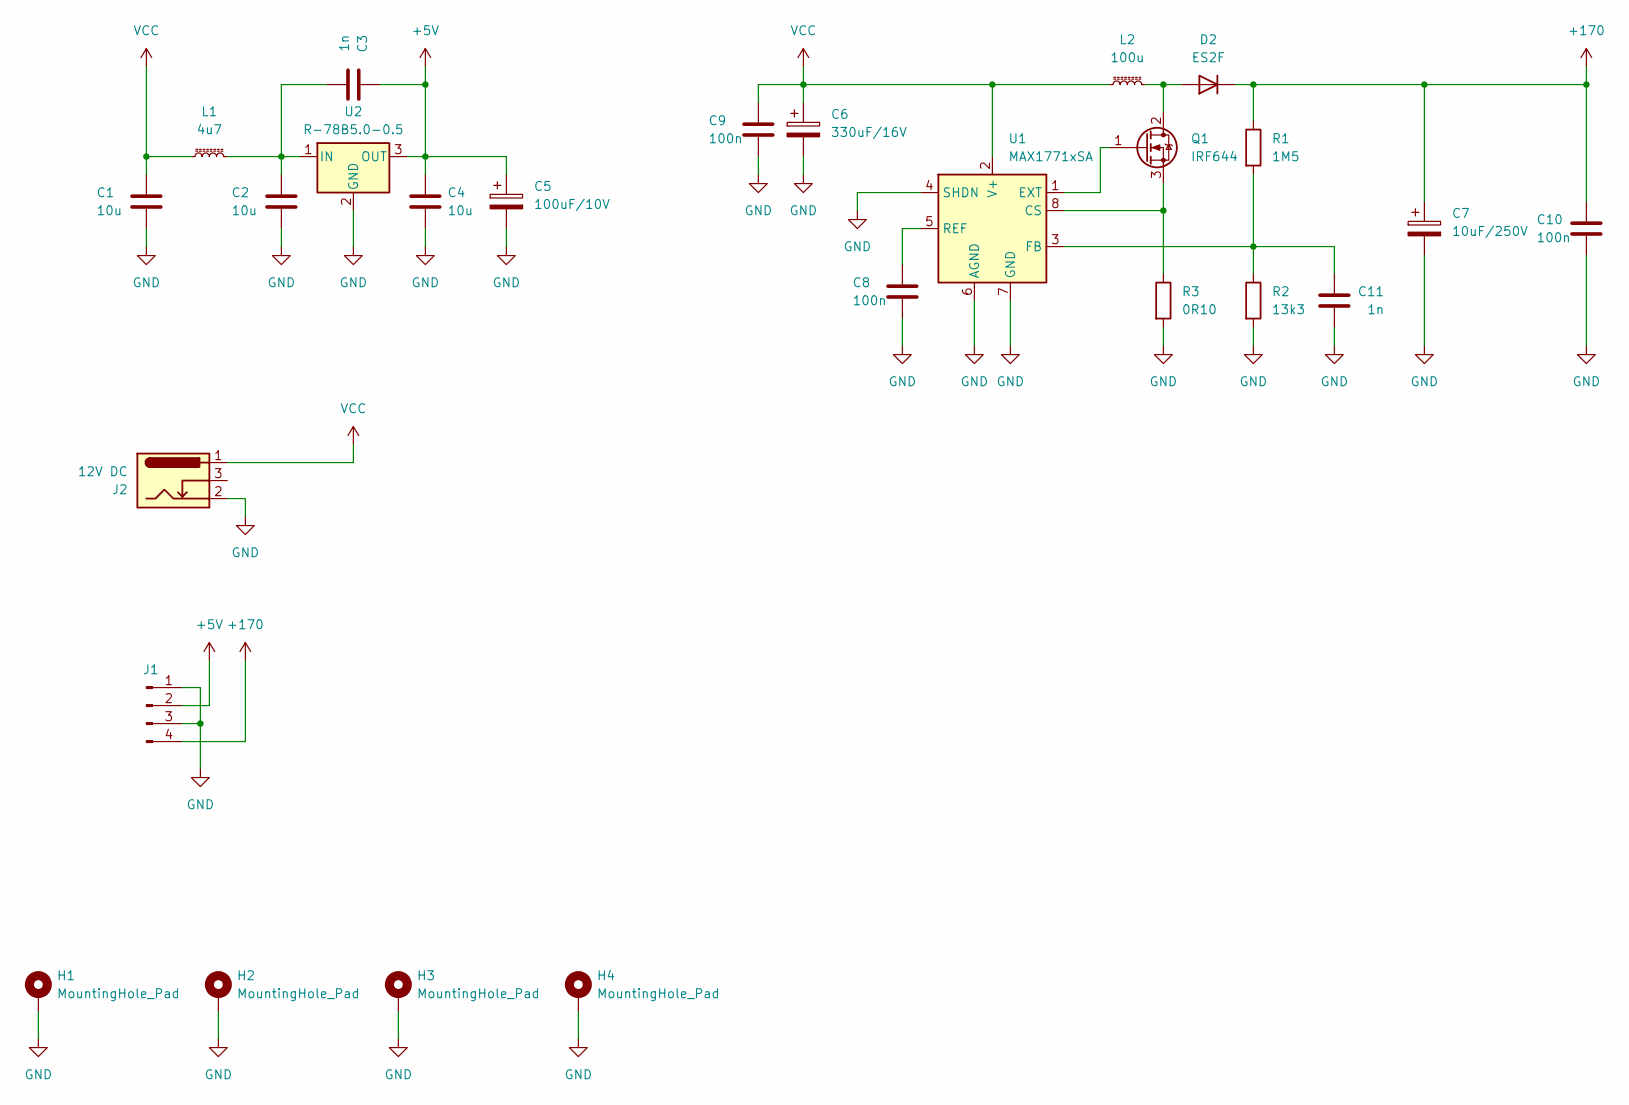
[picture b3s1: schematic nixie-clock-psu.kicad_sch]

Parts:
C1, C2, C4: 10u; C_0805_2012Metric_Pad1.18x1.45mm_HandSolder
C3, C11: 1n; C_0805_2012Metric_Pad1.18x1.45mm_HandSolder
C5: 100uF/10V; CP_Elec_5x5.3
C6: 330uF/16V; CP_Elec_6.3x7.7
C7: 10uF/250V; CP_Elec_10x12.5
C8, C9, C10: 100n; C_0805_2012Metric_Pad1.18x1.45mm_HandSolder
D2: ES2F; D_SMB
H1, H2, H3, H4: MountingHole_Pad; MountingHole_2.7mm_M2.5_DIN965_Pad
J1: Conn_01x04_Pin; PinSocket_1x04_P2.54mm_Vertical
J2: 12V DC; BarrelJack_GCT_DCJ200-10-A_Horizontal
L1: 4u7; L_Changjiang_FNR4030S
L2: 100u; L_Sunlord_SWPA8040S
Q1: IRF644; TO-263-2
R1: 1M5; R_1206_3216Metric
R2: 13k3; R_1206_3216Metric
R3: 0R10; R_1206_3216Metric
U1: MAX1771xSA; SO-8_3.9x4.9mm_P1.27mm
U2: R-78B5.0-0.5; 78xx-05A

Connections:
+5V: C3.2, C4.2, C5.1, J1.2, U2.3 (OUT)
+170: C7.1, C10.2, D2.1 (K), J1.4, R1.1
GND: C1.1, C2.1, C4.1, C5.2, C6.2, C7.2, C8.1, C9.1, C10.1, C11.1, H1.1, H2.1, H3.1, H4.1, J1.1, J1.3, J2.2, R2.2, R3.2, U1.4 (SHDN), U1.6 (AGND), U1.7 (GND), U2.2 (GND)
unnamed: D2.2 (A), L2.2, Q1.2 (D)
unnamed: Q1.1 (G), U1.1 (EXT)
unnamed: Q1.3 (S), R3.1, U1.8 (CS)
unnamed: C11.2, R1.2, R2.1, U1.3 (FB)
unnamed: C8.2, U1.5 (REF)
unnamed: C2.2, C3.1, L1.2, U2.1 (IN)
VCC: C1.2, C6.1, C9.2, J2.1, L1.1, L2.1, U1.2 (V+)
